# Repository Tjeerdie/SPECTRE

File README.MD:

# Project SPECTRE
Project SPECTRE	(Speeduino PrintEd Circuit board TjeeRdiE). This is a PCB with the hardware to run speeduino on a STM32F407VE6T board from ebay. (Or a STM32 BLACK_F407VE as it is sometimes called). 

Schematics and more information on the cpu board can be found here: (https://github.com/mcauser/BLACK_F407VE)

The case with connectors can be found here: https://nl.aliexpress.com/item/32839361268.html?spm=a2g0z.12010615.8148356.7.1da330edPBhz16

Latest tested version by author is 0.5.3. Version 0.5.4 is a cleaned up schematic plus a change to use resistor arrays rather than individual resistors by @vitorboss. The 0.5.4 version is not build and tested but functionally identical to 0.5.3. 

The design is provided as is. Just as it is stated in the license. The design is a hobby project and not specificly designed to adhere to any standard, so use it at your own risk.

A stand alone Peak and Hold injector driver board is now in a seperate repository. See: https://github.com/Tjeerdie/Peak-And-hold-Driver

## Getting Started
Take a look at the very informative manual for speeduino:
https://speeduino.com/Speeduino_manual.pdf

There is a difference for the TPS with respect to the manual. The TPS must be fed by 3.3V and not 5V like the other speeduino boards. For best performance it is better to wire all the grounds of the sensors to the GND pins and not use the PWR_GND or carchassis for this. 

How to load the firmware to the STM32 see:
https://speeduino.com/forum/viewtopic.php?f=13&t=1914&p=26572#p26572

## Board pinout

The TS Mapping column is the pin you enter in the "Local Auxillary Input Channel Configuration" when repurposing the input pins for another purpose (example: oil pressure sensor):
https://speeduino.com/forum/viewtopic.php?f=14&t=2809

| Pin# | Function   | Alternative | Switch | Tuner Studio Mapping |
|-----|-------------|-------------|--------|------------|
| 1   | GND_PWR     |             |        |            |
| 2   | GND_PWR     |             |        |            |
| 3   | 12V_ECU     |             |        |            |
| 4   | 12V_ECU     |             |        |            |
| 5   | INJ_CH8     |             |        | 66         |
| 6   | INJ_CH7     |             |        | 67         |
| 7   | INJ_CH5     |             |        | 62         |
| 8   | INJ_CH6     |             |        | 64         |
| 9   | IDLE1-OUT   | STEP_1A_OUT | JP5    |            |
| 10  | BARO        |             |        | A13         |
| 11  | Spare_2_out | Step_2B_OUT | JP6    | 71         |
| 12  | Spare_1_Out | Step_1B_OUT | JP7    | 72         |
| 13  | IGN_CH1     |             |        |            |
| 14  | 02_2        |             |        | A4         |
| 15  | FAN         |             |        |            |
| 16  | IDLE2-OUT   | STEP_2A_OUT | JP8    |            |
| 17  | IAT         |             |        |            |
| 18  | IAT_2       |             |        | A0         |
| 19  | FUEL_PUMP   |             |        |            |
| 20  | CLT_2       |             |        | A1         |
| 21  | RS232_TX    |             |        |            |
| 22  | GND         | IGN5-OUT    | JP18   |            |
| 23  | O2          |             |        |            |
| 24  | INJ_CH4     |             |        |            |
| 25  | MAP         |             |        |            |
| 26  | GND         | IGN6-OUT    | JP16   |            |
| 27  | CLT         |             |        |            |
| 28  | INJ_CH3     |             |        |            |
| 29  | CANH        |             |        |            |
| 30  | GND         |             |        |            |
| 31  | IGN_CH2     |             |        |            |
| 32  | INJ_CH1     |             |        |            |
| 33  | GND         |             |        |            |
| 34  | RS232_RX    |             |        |            |
| 35  | TPS         |             |        |            |
| 36  | IGN_CH3     |             |        |  24        |
| 37  | 5V          |             |        |            |
| 38  | FLEX_IN     |             |        |            |
| 39  | VR2-        |             |        |            |
| 40  | IGN_CH4     |             |        |  34        |
| 41  | VR2+        |             |        |            |
| 42  | VR1-        |             |        |            |
| 43  | VR1+        |             |        |            |
| 44  | INJ_CH2     |             |        |            |
| 45  | CANL        |             |        |            |
| 46  | 3.3V        |             |        |            |
| 47  | BOOST-OUT   |             |        |            |
| 48  | TACHO-OUT   |             |        |            |

## Jumper settings
There are 12 jumpers on the board to set/change various hardware configurations to suit your needs. with a sharp object scratch away the default bridge and use a solder bridge between the alternative configuration pins. The pull up resitors (JP1/JP4) are briged vs non bridged and no need to skratch anything away.
| JP# | Function                  | Default       | Alternative|
|-----|---------------------------|---------------|------------|
| 1   | Halleffect Pullup resistor| Not Conneced  | Connected  |
| 2   | Halleffect or VR input VR1| VR            | Hall       |
| 3   | Halleffect or VR input VR2| Hall          | VR         |
| 4   | Halleffect Pullup resistor| Not Conneced  | Connected  |
| 5   | STEP_1A_out or IDLE1-OUT  | IDLE1-OUT     | STEP_1A_OUT|
| 6   | Spare_2_out or Step_2B_OUT| Spare_2_out   | Step_2B_OUT|
| 7   | Spare_1_Out or Step_1B_OUT| Spare_1_Out   | Step_1B_OUT|
| 8   | IDLE2-OUT or STEP_2A_OUT  | IDLE2-OUT     | STEP_2A_OUT|
| 9  | Tacho out voltage		  | 12V output     | 5V output |
| 10  | Ignition trigger out voltage		  | 5V output     | 12V output |
| 15  | Flex fuel or Boot0 in     | Flexfuel      | Boot0      |
| 16  | Ignition 6 or GND         | GND           | IGN6       |
| 18  | Ignition 5 or GND   _     | GND           | IGN5       |

## Information for assembling a V0.5.X board
Information for board assembly and choosing components. If  you plan to build one of these it is important to note that a little electronic knowledge is very helpful if not essential to get the board working. The accompanying JLC bom list has most passive components in it, but not all components, some self assembly/soldering and part selection is required.  

### RS232 and bluetooth
The hardware serial port 1 is shared between bluetooth and RS232 output on the ECU connector. So that means you can only build it with the bluetooth module in place OR the max232 ic in place not both! That will break the communication. 

Dont forget to configure the bluetooth module to use 115200 bps baudrate using the HC-05/HC-06 AT commands. 

If you want your main/Tuner studio communiation to use the hardware serial port 1 (So bluetooth or RS232 on the ECU connector). Build the speeduino firmware in the arduino IDE with no "usb support" -> "None". In that case it will default to use hardware serial 1 as the communication.

If the bluetooth comms are not working and you are using a HC-05 or HC-06 module (both are 3.3v so its safe to direcly connect to the MCU). For V0.5.2 of SPECTRE [R37,R38] can be replaced by 0 ohms. For V0.5.3 [R38] can be replaced by 0 ohm. 

### Zener diodes
If you build the board with the injector driver mosfets to be BSP78 [Q10,Q11,Q13,Q14,Q18,Q19,Q20,Q21] you can leave the bzx84C39 + 1N4148 out [33,D34,D35,D36,D37,D38,D39,D40,D41,D42,D43,D44,D45,D46,D47,D48]. These are used for clamping, but the BSP78 has internal clamping. You can use other mosfets with SOT223 footprint in place of the BSP78. If these are not clamped or reptetative avalanch rated use the clamping diodes to keep them in spec.

### Vehicle Speed input
Note: This workaroud is no longer working. There is no solution yet.

Here is a description how to use one of the analog spare inputs (IAT_2 = ECU pin 18) as VSS input for speeduino. This can be a hall type sensor or a porximity sesnsor. it can NOT be a VR type sensor
1. Remove C2 and C4 from the board
2. On the MCU pin headers of the board connect PA0 to PA2 with a bit of solder
3. in Tuner Studio select pin 50 (PA2) for the VSS input pin.

PA0 (pin 48 in TS) can not work as VSS pin because of conflicting interrupts with the crank sensor (PE0)

## Tested on V0.5.2/V0.5.3
The following functions have been tested and confirmed to be working on a volvo B230FK redblock engine. This a 4 cylinder engine with small turbo. A VAG wasted spark coil with internal drivers is used as ignition<br/> 

VR2 input (Trigger 2) [OK]<br/> 
Halleffect trigger input (Trigger 1) [OK]<br/>
VR1 input (Trigger 1) [OK] <br/> 
Halleffect trigger input (Trigger 2) [OK]<br/>
Manifold Absolute pressure (MAP) [OK]<br/>
Injector outputs [OK]<br/>
Lambda sensor (O2) [OK]<br/>
Throttle position input [OK]<br/>
Bluetooth module (PA9,PA10) [OK]<br/>
Battery voltage reading [OK]<br/> 
Ignition outputs [OK]<br/> 
Fuel pump relay [OK]<br/>
FAN relay [OK]<br/>
PWM idle output [OK]<br/>
Coolant temperature (CLT) [OK]<br/>
Inlet Air Temperature (IAT) [OK]<br/>
RS232 TX [OK]<br/>
RS232 RX [OK]<br/>
BOOST output [OK]<br/>
Stepper idle output [OK]<br/> 
TACHO out [OK]<br/>

## To be tested on V0.5.2/V0.5.3
BARO <br/>
CAN bus TX<br/>
CAN bus RX<br/>
FLEX fuel input<br/>
Coolant temperature (CLT_2) <br/>
Inlet Air Temperature (IAT_2) <br/>
Lambda sensor (O2_2) <br/>

## License
This project is licensed under the GNU GENERAL PUBLIC LICENSE - see the [LICENSE.md](LICENSE.md) file for details

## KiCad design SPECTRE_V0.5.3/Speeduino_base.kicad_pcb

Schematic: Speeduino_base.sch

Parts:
A1: Pololu_Breakout_DRV8825; Pololu_Breakout-16_15.2x20.3mm
C1, C2, C9, C10, C13, C19, C21, C22, C25, C26, C29, C31, C32: 100nf; C0603
C3, C4, C8, C14, C16, C17, C20, C23, C24, C27, C28: 220nf; C0603
C5, C7: 1nf; C0603; LCSC C1588
C6: 10uf; C1206
C11: 220nf; C0603; LCSC C21120
C12, C18: 470uF 6.3V; CP_Elec_6.3x7.7; LCSC C250105
C15: 10uf; C1206; LCSC C13585
C30: 100nf; C0603; LCSC C14663
D1, D2, D3, D5, D7, D9, D10, D11, D12, D15, D16, D17, D19, D21, D24: BAT54S; SOT23
D4, D14, D20, D30, D31: 1N4007; D_SMA
D6: Zener 3.6V; D_MiniMELF_Handsoldering
D8: Zener 5.1V; D_MiniMELF_Handsoldering
D13, D18, D26, D27, D29: YEL; LED-0603
D22: BAT54S; SOT23; LCSC C19726
D28: YEL; LED-0603; LCSC C72038
D32: 1N4007; D_SMA; LCSC C110856
D33, D35, D36, D39, D40, D43, D44, D45: 1N4148WS; D_SOD-323
D34, D37, D38, D41, D42, D46, D47, D48: BZX84C39; D_SOT-23_ANK
F1, F2: PPTC 16V2A; R_1812_4532Metric_Pad1.30x3.40mm_HandSolder; LCSC C70122
J1: Conn_01x06_Male; PinHeader_1x06_P2.54mm_Vertical
J2: Conn_02x04_Odd_Even; PinHeader_2x04_P2.54mm_Vertical
J3: ProtoArea; Proto_area
JP1, JP4: Jumper_NO_Small; SolderJumper-2_P1.3mm_Open_Pad1.0x1.5mm
JP2, JP3, JP5, JP6, JP7, JP8, JP9, JP10, JP15, JP16, JP18: SolderJumper_3_Bridged12; SolderJumper-3_P1.3mm_Bridged12_Pad1.0x1.5mm
JP11, JP12: PINHD-2X24; 2X24
JP13: Jumper_NC_Small; SolderJumper-2_P1.3mm_Bridged_Pad1.0x1.5mm
JP14: Jumper_NO_Small; PinHeader_1x02_P2.54mm_Vertical
Q1: AO3400; SOT-23; LCSC C344010
Q6, Q7, Q12: AO3400; SOT-23
Q10, Q11, Q13, Q14, Q15, Q16, Q17, Q18, Q19, Q20, Q21: BSP78; SOT223
R1, R42, R57: 2k49; R0603
R2: VARISTOR-18V; RV_Disc_D12mm_W3.9mm_P7.5mm
R3, R12, R15, R21, R32, R65, R68, R69: 1k; R0603
R4, R6, R8, R18, R24, R27, R33, R37, R41, R49, R50, R55, R60, R61, R64, R77: 470R; R0603
R5, R11, R13, R14, R16, R19, R36, R59, R66, R79, R80, R81, R82, R86, R87, R88, R89, R91, R92: 10k; R0603
R7, R17, R38, R58, R62, R63: 10R; R_0603_1608Metric_Pad1.05x0.95mm_HandSolder
R9, R28, R46: 4k7; R0603
R10, R29, R47: 9k1; R0603
R20: 0R0; R0603; LCSC C21189
R22, R31: 2k49; R0603; LCSC C126158
R23: 470R; R0603; LCSC C23179
R25: 4k7; R0603; LCSC C23162
R26: 9k1; R0603; LCSC C23260
R30: 1k8; R0603; LCSC C21190
R34, R39, R43, R48, R51, R52, R53, R54, R56, R67, R76, R78, R83, R84, R85: 100R; R0603
R35: 1k; R0603; LCSC C21190
R40: 100R; R0603; LCSC C22775
R44: 33k; R0603; LCSC C4216
R45: 5k1; R0603; LCSC C23186
R70: 10R; R_0603_1608Metric_Pad1.05x0.95mm_HandSolder; LCSC Part # C22859
R71: 10R; R_0603_1608Metric_Pad1.05x0.95mm_HandSolder; LCSC C22859
R74: 120R; R0603; LCSC C22787
R75: 220R; R0603; LCSC C22962
R90: 10k; R0603; LCSC C25803
U1: MAX9926UAEE+; 21-0055H_16
U2: LM78M05_TO220; TO-220-3_Horizontal_TabUp
U3: TL431DBZ; SOT-23
U4: molex_48pin; Molex_48
U5: TJA1050; SO-8_5.3x6.2mm_P1.27mm; LCSC C6952
U6: MAX3232; SOIC-16_4.55x10.3mm_P1.27mm
U7, U8, U9, U10: MIC4427; SO-8_3.9x4.9mm_P1.27mm; LCSC C49058
U$1: WIRELESS-BLUETOOTH-HC-05

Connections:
3.3V: A1.2 (~FLT), A1.13 (~RST), A1.14 (~SLP), C12.1, D1.2 (C2), D2.2 (C2), D3.2 (C2), D5.2 (C2), D6.1 (K), D7.2 (C2), D9.2 (C2), D10.2 (C2), D11.2 (C2), D12.2 (C2), D15.2 (C2), D16.2 (C2), D17.2 (C2), D19.2 (C2), D21.2 (C2), D22.2 (C2), D24.2 (C2), J1.1, J3.5, JP11.5, JP11.6, JP11.7, JP11.8, JP12.1, JP12.2, JP12.3, JP12.4, JP14.2, R1.2, R12.2, R15.2, R22.2, R30.1, R42.2, R57.2, R76.2, R78.2, U3.1 (K), U4.46, U6.16 (VCC)
5V: C15.2, C17.2, C18.1, D8.1 (K), J3.41, JP1.2, JP4.2, JP9.3 (B), JP10.1 (A), JP11.1, JP11.2, JP11.3, JP11.4, R75.2, U1.14 (VCC), U2.3 (VO), U4.37, U5.3 (vcc), U$1.5 (+5V)
/BT_TX: R37.2, U$1.3 (TX)
AIN_1: C2.2, R1.1, R6.1, U4.18
AIN_2: C1.2, R4.1, U4.14
AIN_3: C26.2, R57.1, R61.1, U4.20
BARO: C19.2, R41.1, U4.10
BME280_CS: J1.5, J2.4
BOOST-OUT: D30.2 (A), Q16.2 (D), Q16.4 (D), U4.47
BOOT0: D24.3 (C1A2), JP12.5, JP14.1, R64.1
BOOT0_EXT: JP15.3 (B), R64.2
BOOT1: JP12.6
CANH: JP13.2, U4.29, U5.7 (CANH)
CANL: R74.2, U4.45, U5.6 (CANL)
CLT: C21.2, R42.1, R49.1, U4.27
FAN: D18.-, D20.2 (A), Q6.3 (D), U4.15
FLEX_FUEL_IN: JP15.1 (A), R32.2
FUEL_PUMP: D13.-, D14.2 (A), Q1.3 (D), U4.19
GND: C1.1, C2.1, C3.1, C4.1, C9.1, C10.1, C11.1, C12.2, C13.1, C14.1, C16.1, C19.1, C20.1, C21.1, C22.1, C23.1, C24.1, C25.1, C26.1, C27.1, C28.1, C29.2, C30.2, D1.1 (A1), D2.1 (A1), D3.1 (A1), D5.1 (A1), D6.2 (A), D7.1 (A1), D9.1 (A1), D10.1 (A1), D11.1 (A1), D12.1 (A1), D15.1 (A1), D16.1 (A1), D17.1 (A1), D19.1 (A1), D21.1 (A1), D22.1 (A1), D24.1 (A1), J1.2, J3.42, J3.44, J3.46, JP11.9, JP11.10, JP12.7, JP12.8, JP12.9, JP12.10, JP16.1 (A), JP18.1 (A), Q12.2 (S), R5.2, R10.1, R16.2, R20.1, R26.1, R29.1, R31.2, R45.1, R47.1, U1.1 (INT_THRS1), U1.3 (BIAS1), U1.6 (BIAS2), U1.8 (INT_THRS2), U1.11 (GND), U1.13 (ZERO_EN), U3.3 (A), U4.30, U4.33, U5.2 (gnd), U5.8 (S), U6.15 (GND), U$1.4 (GND)
IAT: C13.2, R22.1, R27.1, U4.17
IDLE1-OUT: D31.2 (A), JP5.1 (A), Q17.2 (D), Q17.4 (D)
IDLE2-OUT: D32.2 (A), JP8.1 (A), Q15.2 (D), Q15.4 (D)
IGN1-OUT: R7.1, U4.13
IGN2-OUT: R17.1, U4.31
IGN3-OUT: R38.1, U4.36
IGN4-OUT: R58.1, U4.40
IGN5-OUT: JP18.3 (B), R62.1
IGN6-OUT: JP16.3 (B), R63.1
INJ1-OUT: D41.1 (K), Q13.2 (D), Q13.4 (D), U4.32
INJ2-OUT: D42.1 (K), Q14.2 (D), Q14.4 (D), U4.44
INJ3-OUT: D34.1 (K), Q18.2 (D), Q18.4 (D), U4.28
INJ4-OUT: D46.1 (K), Q19.2 (D), Q19.4 (D), U4.24
INJ5-OUT: D37.1 (K), Q10.2 (D), Q10.4 (D), U4.7
INJ6-OUT: D47.1 (K), Q20.2 (D), Q20.4 (D), U4.8
INJ7-OUT: D38.1 (K), Q11.2 (D), Q11.4 (D), U4.6
INJ8-OUT: D48.1 (K), Q21.2 (D), Q21.4 (D), U4.5
MAP: C9.2, R23.1, U4.25
unnamed: C3.2, R4.2, R9.1
unnamed: C5.1, R13.2, U1.15 (IN1-)
unnamed: C5.2, R11.2, U1.16 (IN1+)
unnamed: C6.2, C8.2, D4.1 (K), U2.1 (VI)
unnamed: C7.1, R19.2, U1.10 (IN2-)
unnamed: C7.2, R14.2, U1.9 (IN2+)
unnamed: C11.2, R23.2, R25.1
unnamed: C14.2, R24.2, R28.1
unnamed: C20.2, R41.2, R46.1
unnamed: C22.2, R44.1, R45.2, R50.1
unnamed: C29.1, U6.6 (VS-)
unnamed: C30.1, U6.2 (VS+)
unnamed: C31.1, U6.1 (C1+)
unnamed: C31.2, U6.3 (C1-)
unnamed: C32.1, U6.4 (C2+)
unnamed: C32.2, U6.5 (C2-)
unnamed: D11.3 (C1A2), R32.1, R35.2
unnamed: D13.+, R33.1
unnamed: D18.+, R55.1
unnamed: D26.+, R75.1
unnamed: D27.+, R76.1
unnamed: D28.+, R77.1
unnamed: D29.+, R78.1
unnamed: D29.-, Q12.3 (D)
unnamed: D33.1 (K), Q18.1 (G), R52.1, R89.1
unnamed: D33.2 (A), D34.2 (A)
unnamed: D35.1 (K), Q10.1 (G), R39.1, R79.1
unnamed: D35.2 (A), D37.2 (A)
unnamed: D36.1 (K), Q11.1 (G), R40.1, R80.1
unnamed: D36.2 (A), D38.2 (A)
unnamed: D39.1 (K), Q13.1 (G), R43.1, R81.1
unnamed: D39.2 (A), D41.2 (A)
unnamed: D40.1 (K), Q14.1 (G), R48.1, R82.1
unnamed: D40.2 (A), D42.2 (A)
unnamed: D43.1 (K), Q19.1 (G), R51.1, R90.1
unnamed: D43.2 (A), D46.2 (A)
unnamed: D44.1 (K), Q20.1 (G), R53.1, R91.1
unnamed: D44.2 (A), D47.2 (A)
unnamed: D45.1 (K), Q21.1 (G), R54.1, R92.1
unnamed: D45.2 (A), D48.2 (A)
unnamed: JP1.1, R3.2
unnamed: JP2.1 (A), R12.1, U1.4 (COUT1)
unnamed: JP2.2 (C), R8.2
unnamed: JP3.2 (C), R18.2
unnamed: JP3.3 (B), R15.1, U1.5 (COUT2)
unnamed: JP4.1, R21.2
unnamed: JP5.2 (C), U4.9
unnamed: JP6.2 (C), U4.11
unnamed: JP7.2 (C), U4.12
unnamed: JP8.2 (C), U4.16
unnamed: JP9.2 (C), R65.2
unnamed: JP10.2 (C), U7.6 (V+), U8.6 (V+), U9.6 (V+)
unnamed: JP13.1, R74.1
unnamed: JP15.2 (C), U4.38
unnamed: JP16.2 (C), U4.26
unnamed: JP18.2 (C), U4.22
unnamed: Q1.1 (G), R34.2, R36.1
unnamed: Q6.1 (G), R56.2, R59.1
unnamed: Q7.1 (G), R66.2, R67.2
unnamed: Q15.1 (G), R83.2, R86.2
unnamed: Q16.1 (G), R84.2, R87.2
unnamed: Q17.1 (G), R85.2, R88.2
unnamed: R7.2, U7.7 (OUT_A)
unnamed: R17.2, U7.5 (OUT_B)
unnamed: R30.2, R31.1, U3.2 (REF)
unnamed: R38.2, U8.7 (OUT_A)
unnamed: R58.2, U8.5 (OUT_B)
unnamed: R62.2, U9.7 (OUT_A)
unnamed: R63.2, U9.5 (OUT_B)
unnamed: R68.2, U5.1 (txd)
unnamed: R69.2, U5.4 (rxd)
unnamed: R70.2, U10.7 (OUT_A)
unnamed: R71.2, U10.5 (OUT_B)
O2: C10.2, R24.1, U4.23
PA0: C4.2, D2.3 (C1A2), JP11.23, R6.2
PA1: C28.2, D19.3 (C1A2), JP11.24, R61.2
PA2: J3.1, JP11.25
PA3: J3.2, JP11.26
PA4: D3.3 (C1A2), JP11.27, R9.2, R10.2
PA5: J3.4, JP11.28
PA6: JP11.29, Q12.1 (G)
PA8: JP12.35, U8.2 (IN_A)
PA9: JP12.34, U6.11 (T1IN), U$1.2 (RX)
PA10: D12.3 (C1A2), JP12.33, R37.1, U6.12 (R1OUT)
PB1: D15.3 (C1A2), JP11.34, R46.2, R47.2
PB3: JP12.18
PB5: JP12.17
PB6: JP12.16
PB7: JP12.15, U9.4 (IN_B)
PB8: JP12.14
PB9: JP12.13, U7.4 (IN_B)
PB10: JP11.44
PB11: JP11.45
PB12: JP11.46, U10.2 (IN_A)
PB13: JP11.47, U10.4 (IN_B)
PB14: JP11.48
PB15: JP12.48
PC0: C16.2, D10.3 (C1A2), JP11.17, R27.2
PC1: C27.2, D21.3 (C1A2), JP11.18, R60.2
PC2: D7.3 (C1A2), JP11.19, R25.2, R26.2
PC3: C23.2, D16.3 (C1A2), JP11.20, R49.2
PC4: D9.3 (C1A2), JP11.31, R28.2, R29.2
PC5: C24.2, D17.3 (C1A2), JP11.32, R50.2
PC6: JP12.39, R84.1
PC7: JP12.38, R85.1
PC8: JP12.37
PC13: JP11.16, R67.1
PD0: D22.3 (C1A2), JP12.26, R69.1
PD1: JP12.25, R68.1
PD3: JP12.23, R83.1
PD4: JP12.22, R35.1
PD5: J3.47, JP12.21
PD6: J3.48, JP12.20
PD7: JP12.19, U7.2 (IN_A)
PD8: JP12.47
PD9: JP12.46, U9.2 (IN_A)
PD10: JP12.45, U8.4 (IN_B)
PD11: JP12.44
PD12: JP12.43, R43.2
PD13: JP12.42, R48.2
PD14: JP12.41, R52.2
PD15: JP12.40, R51.2
PE0: D1.3 (C1A2), JP12.12, R5.1, R8.1
PE1: D5.3 (C1A2), JP12.11, R16.1, R18.1
PE2: A1.9 (~EN), JP11.11
PE3: JP11.12, R34.1
PE4: JP11.13
PE5: A1.15 (STEP), JP11.14
PE6: JP11.15, R56.1
PE7: A1.16 (DIR), JP11.35
PE8: J3.6, JP11.36
PE9: JP11.37, R39.2
PE10: JP11.38
PE11: JP11.39, R53.2
PE12: JP11.40
PE13: JP11.41, R54.2
PE14: JP11.42, R40.2
PE15: JP11.43
PWR_GND: A1.1 (GND), A1.7 (GND), C6.1, C8.1, C15.1, C17.1, C18.2, D8.2 (A), D26.-, D27.-, D28.-, Q1.2 (S), Q6.2 (S), Q7.2 (S), Q10.3 (S), Q11.3 (S), Q13.3 (S), Q14.3 (S), Q15.3 (S), Q16.3 (S), Q17.3 (S), Q18.3 (S), Q19.3 (S), Q20.3 (S), Q21.3 (S), R2.1, R20.2, R36.2, R59.2, R66.1, R79.2, R80.2, R81.2, R82.2, R86.1, R87.1, R88.1, R89.2, R90.2, R91.2, R92.2, U2.2 (GND), U4.1, U4.2, U7.3 (GND), U8.3 (GND), U9.3 (GND), U10.3 (GND)
RS232_RX: U4.34, U6.13 (R1IN)
RS232_TX: U4.21, U6.14 (T1OUT)
SPI1_MISO: J1.6, J2.7
SPI1_MOSI: J1.4, J2.6
SPI1_SCK: J1.3, J2.5
STEP_1A_OUT: A1.4 (A1), JP5.3 (B)
STEP_1B_OUT: A1.5 (B1), JP7.3 (B)
STEP_2A_OUT: A1.3 (A2), JP8.3 (B)
STEP_2B_OUT: A1.6 (B2), JP6.3 (B)
Spare_1-Out: JP7.1 (A), R71.1
Spare_2-Out: JP6.1 (A), R70.1
TACHO-OUT: Q7.3 (D), R65.1, U4.48
TPS: C25.2, R60.1, U4.35
VBAT: D14.1 (K), D20.1 (K), D30.1 (K), D31.1 (K), D32.1 (K), F1.1, F2.1, J3.43, R2.2, R33.2, R44.2, R55.2, R77.2, U4.3, U4.4
VBAT_F1: D4.2 (A), F1.2, JP9.1 (A), JP10.3 (B)
VR1+: JP2.3 (B), R3.1, R11.1, U4.43
VR1-: R13.1, U4.42
VR2+: JP3.1 (A), R14.1, R21.1, U4.41
VR2-: R19.1, U4.39
V_IDLE: A1.8 (VMOT), F2.2, U10.6 (V+)

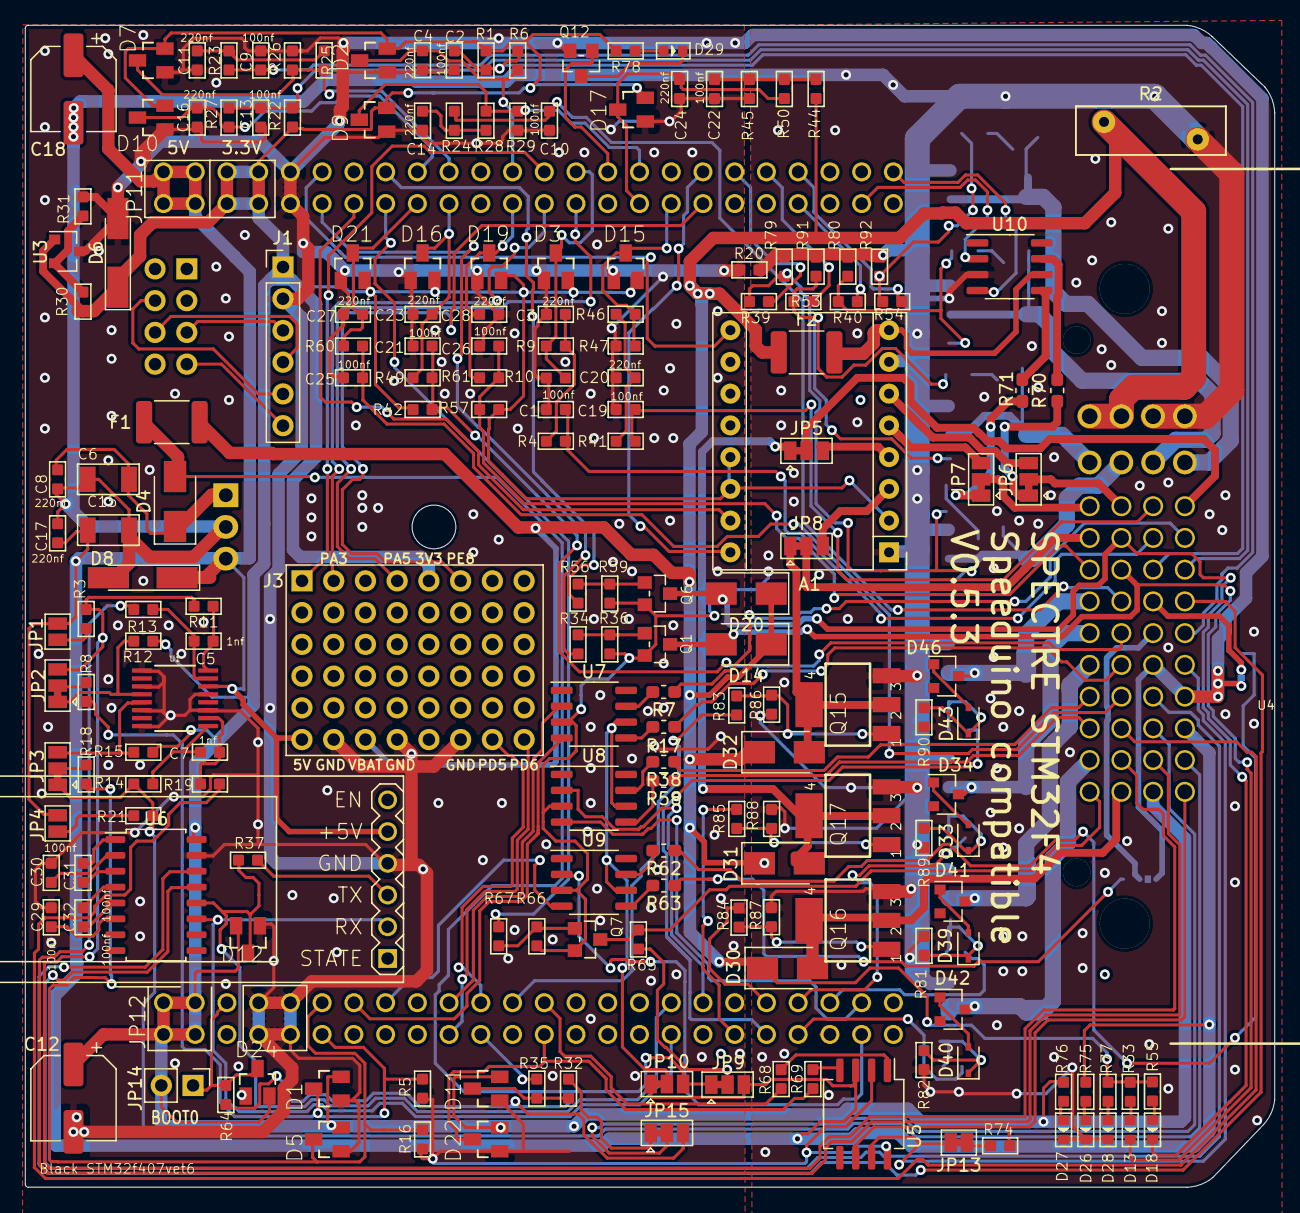
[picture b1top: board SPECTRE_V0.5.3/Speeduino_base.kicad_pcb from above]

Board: 2 copper layers, 100.0 x 93.0 mm, 217 parts (0 on the bottom side), 180 nets.

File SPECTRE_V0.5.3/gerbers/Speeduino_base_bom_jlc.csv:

"Comment","Designator","Footprint","LCSC Part #"
"1nf","C5,C7","C0603","C1588"
"10uf","C6,C15","C1206","C13585"
"470uF 6.3V","C12,C18","CP_Elec_6.3x7.7","C250105"
"220nf","C17,C28,C8,C27,C23,C20,C16,C4,C24,C11,C14,C3","C0603","C21120"
"100nf","C31,C30,C32,C29,C26,C25,C21,C19,C13,C2,C22,C9,C10,C1","C0603","C14663"
"BAT54S","D12,D1,D5,D11,D19,D24,D22,D21,D16,D15,D10,D2,D17,D7,D9,D3","SOT23","C19726"
"YEL","D18,D28,D27,D26,D29,D13","LED-0603","C72038"
"1N4007","D31,D20,D4,D30,D32,D14","D_SMA","C110856"
"PPTC 16V2A","F1,F2","R_1812_4532Metric_Pad1.30x3.40mm_HandSolder","C70122"
"AO3400","Q6,Q12,Q7,Q1","SOT-23","C344010"
"10R","R7,R17,R38,R58,R62,R63,R70,R71","R_0603_1608Metric_Pad1.05x0.95mm_HandSolder","C22859"
"1k","R12,R15,R21,R32,R35,R3,R69,R65,R68","R0603","C21190"
"0R0","R20","R0603","C21189"
"1k8","R30","R0603","C21190"
"33k","R44","R0603","C4216"
"5k1","R45","R0603","C23186"
"4k7","R46,R25,R28,R9","R0603","C23162"
"9k1","R47,R26,R29,R10","R0603","C23260"
"470R","R55,R37,R61,R77,R8,R18,R64,R33,R60,R49,R41,R27,R6,R50,R23,R24,R4","R0603","C23179"
"100R","R56,R85,R76,R78,R52,R84,R83,R51,R39,R53,R40,R54,R48,R43,R67,R34","R0603","C22775"
"2k49","R57,R31,R42,R22,R1","R0603","C126158"
"10k","R59,R11,R13,R14,R19,R88,R5,R16,R87,R86,R89,R90,R79,R91,R80,R92,R82,R81,R66,R36","R0603","C25803"
"120R","R74","R0603","C22787"
"220R","R75","R0603","C22962"
"TJA1050","U5","SO-8_5.3x6.2mm_P1.27mm","C6952"
"MIC4427","U7,U8,U9,U10","SO-8_3.9x4.9mm_P1.27mm","C49058"
